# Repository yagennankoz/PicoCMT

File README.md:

**日本語** | [English](README_en.md)

# PicoCmt - 8bit PC用 CMT(カセット磁気テープ) エミュレータ

Raspberry Pi Pico W を使用した、8bitレトロPC向けのカセット磁気テープ（CMT）エミュレータです。
SDカードに保存されたテープイメージファイルを実機へ音声信号としてロードしたり、実機からのセーブ音声を録音してテープイメージに変換・保存することができます。
Wi-Fi経由で、PCやスマホのブラウザからSDカードのファイルを操作したり、USBでつないだPCからSDカードをUSBドライブとして読み書きしたりすることもできます。

## 主な機能
* **ファイルからの再生 (LOAD)**
  * 対応フォーマット:

    | 拡張子         | 主な機種                                                      | 実機での確認       |
    | -------------- | ------------------------------------------------------------- | ------------------ |
    | `.T88`         | PC-8801 / PC-8001 (タグ形式)                                  | 確認済み (PC-8801) |
    | `.CMT`         | PC-8801 / PC-8001 (ベタ形式)                                  | 確認済み (PC-8801) |
    | `.P6` / `.P6T` | PC-6001                                                       | **未確認**         |
    | `.CAS`         | MSX                                                           | 確認済み           |
    | `.T77`         | FM-7                                                          | **未確認**         |
    | `.RAW`         | 機種を問わない (録音したままの波形。PicoCmt 独自の形式)       | 確認済み (PC-8801) |
    | `.WAV`         | 機種を問わない (テープの音声を録った WAV ファイル。リニアPCM) | 確認済み (PC-8801) |

    PC-6001 (`.P6` / `.P6T`) と FM-7 (`.T77`) は、実機でもエミュレータでも動作確認をしていません。
    MP3 などの圧縮した音声には対応していません。
    WAV は波形をそのまま出すので、録音の状態が悪いと読めないことがあります。そのときは T88 などに変換してから再生してください (変換するときれいな波形で出し直します)。
  * ファイル内のデータをFSK音声信号に変換し、PCへ出力します。
  * PCのREMOTE端子 (カセットのモーター制御) に連動して、再生の開始・一時停止を自動で行います。
  * T88 は無音区間 (ブランク) の前後へ頭出しできます。
  * T88 の DATA タグの形式 (ボーレート・パリティ・ストップビット長) どおりに出力します。
  * 一覧に出すファイルを拡張子で絞り込めます。
* **実機からの録音・変換 (SAVE)**
  * PCからの出力音声を録音し、自動的に上記のいずれかの形式に変換してSDカードに保存します。
  * ボーレート (600 / 1200 / 2400) は録音した信号から自動で判別します。
  * 録音したデータに含まれるプログラム名を読み取り、ファイル名を自動で付けます。
  * 既存ファイルへの追記録音 (アペンド) にも対応しています (`.T88` / `.T77` / `.CAS` / `.P6T`)。
  * 1つのブロックの中で 600 / 1200 ボーが切り替わるテープや、パリティ付きのデータも `.T88` に記録できます。
  * 変換せずに、録音したままの波形を `.RAW` として保存することもできます。形式は [RAW_FORMAT.md](RAW_FORMAT.md) を参照してください。
* **RAW / WAV からの変換**
  * `.RAW` と `.WAV` を、本体で上の各形式に変換できます。データの中のプログラム名でファイル名を付けます。
* **Wi-Fi / Webファイルマネージャ機能**
  * Pico W のWi-Fi機能を利用し、内蔵のWebサーバーを起動できます。
  * SDカードを抜き差しすることなく、PCやスマホのブラウザから `http://picocmt.local/` を開いて、ファイルのアップロード・ダウンロード・削除・名前の変更・フォルダの作成ができます。
  * 複数のファイルをまとめて選ぶと、1つずつ順番にアップロード・ダウンロードします。
  * ログイン (ID/パスワード) の ON/OFF とパスワードは本体の設定メニューで変更できます。
  * Wi-Fi接続中はNTPで時刻を合わせ、録音したファイルに日時を付けます (日本版は日本時間、全世界共通版はUTC)。
  * 再生・録音中は、Wi-Fiの通信で電源が揺れて信号が乱れないよう、Wi-Fiを自動で切断し、終わったらつなぎ直します。
  * **Wi-Fiを使うときは、ACアダプタ (USB充電器) など、電流に余裕のある電源の使用をお勧めします。** Wi-Fiの通信には大きな電流が流れるため、PCのUSB端子やUSBハブからの給電では動作が不安定になることがあります。
  * 設定したWi-Fiパスワード等は、本体固有のIDで暗号化してEEPROMに保存します。
    ただし、本体を入手した人はフラッシュメモリから取り出せる可能性があります。気になる場合は、ゲスト用やIoT機器用のWi-Fiを使ってください。
* **USBドライブ機能**
  * USBでPCにつなぐと、SDカードをPCのUSBドライブとして読み書きできます (SDカードを抜き差しせずにファイルをコピー・削除できます)。
  * 電源を入れたときにPCとつながっていれば、USBドライブにするかを最初に聞きます。設定メニューからも始められます。
  * USBドライブの間は、SDカードが壊れないよう、再生・録音・ファイルブラウザを止め、Wi-Fiも切断します。PCで取り出すか、本体の [STOP] でやめると元に戻ります。

---

## 必要なハードウェア

基板のガーバーデータは`hardware/JLCPCB`を参照してください。JLCPCB等に発注することでプリント基板の生産が可能です。
主要な部品構成は以下の通りです。詳細な部品リストや定数は `hardware/parts.md` を参照してください。

* **マイコンボード:** Raspberry Pi Pico W
  * **電源:** PCのUSB端子やUSBハブ (セルフパワーのものも含む) から給電していると、Wi-Fiの通信で電源が不安定になり、ロード・セーブがエラーになることがあるため (PC-8801 で確認)、ロード・セーブ中はWi-Fiを自動で切断します。**Wi-Fiを使うときは、ACアダプタ (USB充電器) など、電流に余裕のある電源から給電してください。**
* **ディスプレイ:** 0.96インチ OLEDディスプレイ (SSD1306 / I2C接続)
* **ストレージ:** MicroSDカードモジュール (SPI接続)
* **アナログ回路:** 
  * オペアンプ `MCP6022` (信号増幅・波形整形用)
  * コンパレータ `LM393` (録音パルス検出用)
  * フォトカプラ `PC817` (REMOTE端子制御用)
* **インターフェース:**
  * タクトスイッチ ×10 (操作用)
  * 3.5mm モノラルジャック ×2 (LOAD用, SAVE用)
  * 2.5mm モノラルジャック ×1 (REMOTE制御用)
  * 圧電ブザー (モニタースピーカー用)

---

## 開発環境とビルド手順

本プロジェクトは **PlatformIO** を使用して開発されています。Arduinoコアには `earlephilhower` 版の Raspberry Pi PicoW/RP2040 コアを使用します。

### 1. インストール
1. リリースに配置されているファームウェアファイル`PicoCMT*.uf2`をダウンロードします。
   ファイル名の末尾は地域の設定です。使う国に合わせて選んでください。

   | ファイル         | 使う国       | Wi-Fiの地域設定        | 時刻                          |
   | ---------------- | ------------ | ---------------------- | ----------------------------- |
   | `PicoCMT_JP.uf2` | 日本         | 日本 (チャンネル1〜13) | 日本時間 (NTP: `ntp.nict.jp`) |
   | `PicoCMT_WW.uf2` | 日本以外の国 | 全世界共通             | UTC (NTP: `pool.ntp.org`)     |
2. PCとRaspberryPi PicoWをUSB接続します。
3. RaspberryPi PicoWの`BOOTSEL`ボタンを押しながら、PicoCMT基板上のRESETボタンを押下します。
4. PC上でRaspberryPi PicoWのフォルダが開かれますので、そこに`PicoCMT*.uf2`をコピーします。
5. RaspberryPi PicoWが自動で再起動され、PicoCMTが起動します。

以前のバージョン (Wi-Fi設定にPINコードを使っていたもの) から更新した場合、保存していたWi-Fi設定は使えなくなります。もう一度設定してください。

### 2. 開発環境の準備
以下はソースコードからビルドする際の手順です。通常は不要です。
1. [Visual Studio Code (VSCode)](https://code.visualstudio.com/) をインストールします。
2. VSCodeの拡張機能から **PlatformIO IDE** をインストールします。
3. リポジトリをクローンしてください。

### 3. PIOファイルのコンパイルについて
PicoのPIO（アセンブリ）コードは、ビルド前に自動的にC/C++のヘッダファイルに変換される仕組みになっています。
`platformio.ini` 内の `extra_scripts = pre:scripts/generate_pio_headers.py` により、ビルド時に自動で `pio/` フォルダ内のファイルが処理され、`include/generated/` ディレクトリにヘッダファイルが出力されます。手動で実行する必要はありません。

### 4. ビルド
1. VSCodeで `PicoCmt` フォルダを開きます。
2. 初回起動時、PlatformIOが自動的に必要なツールチェーンとライブラリ（Adafruit GFX, SSD1306等）をダウンロードします。
3. 画面下のPlatformIOツールバーから **[✓] Build** をクリックしてビルドを実行します。
   地域ごとの2つのファームウェアがまとめてビルドされ、`.pio/build/<環境名>/PicoCMT_<地域>.uf2` に出力されます。

| 環境名       | 出力ファイル     | Wi-Fiの地域設定                        | 時刻                      |
| ------------ | ---------------- | -------------------------------------- | ------------------------- |
| `rpipico_ww` | `PicoCMT_WW.uf2` | 全世界共通 (`CYW43_COUNTRY_WORLDWIDE`) | UTC                       |
| `rpipico_jp` | `PicoCMT_JP.uf2` | 日本 (`CYW43_COUNTRY_JAPAN`)           | 日本時間 (`FW_REGION_JP`) |

書き込み (Upload) は環境を1つ指定して行ってください。例: `pio run -e rpipico_jp -t upload`

---

## 使い方・操作方法

操作方法については、付属の **[操作マニュアル](MANUAL.md)** を参照してください。
基本的なUI操作、再生（LOAD）・録音（SAVE）の手順、ボーレートの変更方法、Wi-Fi/Webファイルマネージャの設定方法、USBドライブの使い方について記載されています。

---

## 注意事項・免責事項

* 本デバイスの接続や使用により発生したいかなる損害（レトロPC本体の故障、データの消失など）についても、開発者は責任を負いません。自己責任でご使用ください。
* PC-6001 (`.P6` / `.P6T`) と FM-7 (`.T77`) は、実機・エミュレータでの動作確認をしていません。
* **Wi-Fiを使うときは、ACアダプタ (USB充電器) など、電流に余裕のある電源から給電してください。** PCのUSB端子やUSBハブからの給電では、Wi-Fiの通信で電源が不安定になることがあります。
* ロード・セーブ中はWi-Fiを自動で切断します (Wi-Fiの通信で電源が不安定になり、レトロPCへのロード・セーブがエラーになることがあるため。PC-8801 で確認)。
* Webファイルマネージャは暗号化されていない通信 (HTTP) を使います。家庭内のネットワークでお使いください。
* 本体を人に譲る・手放すときは、設定メニューの `WiFi Config` (アクセスポイントを選ぶ画面で [LEFT]) で、保存されているWi-Fi設定を消去してください。
* USBドライブの間に、PCで取り出さずにUSBケーブルを抜いたりSDカードを抜いたりすると、書き込み中のファイルが壊れることがあります。

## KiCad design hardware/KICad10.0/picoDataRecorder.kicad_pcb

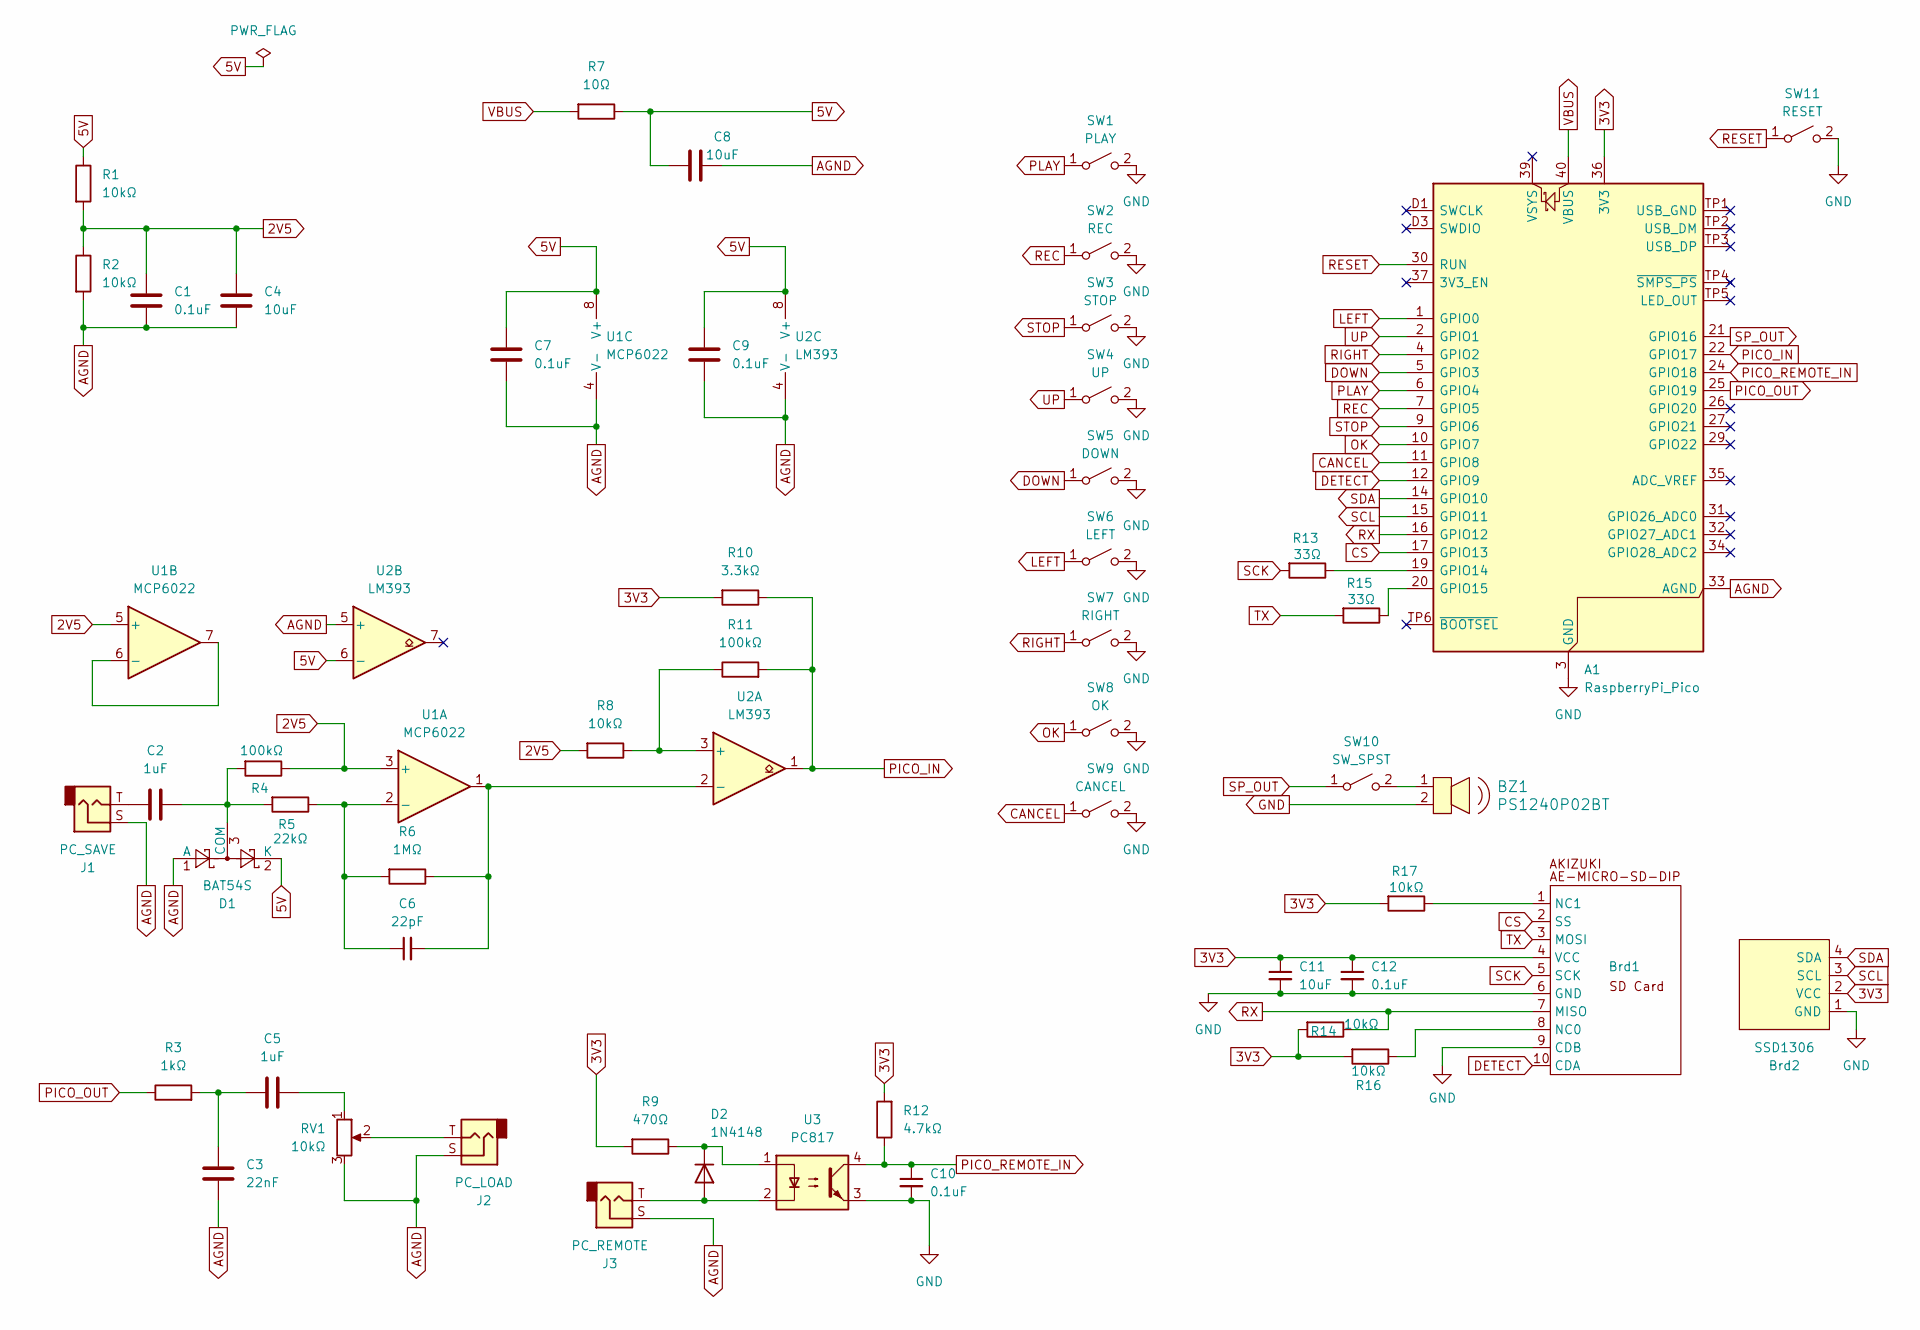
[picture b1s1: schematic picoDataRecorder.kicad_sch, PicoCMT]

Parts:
A1: RaspberryPi_Pico; RaspberryPi_Pico_Common_Unspecified
BZ1: PS1240P02BT; Piezo_Transducer_THT_PS1240P02BT; MPN PS1240P02BT; Digi-Key_PN 445-2525-1-ND
Brd1: AE-MICRO-SD-DIP
Brd2: SSD1306; 128x64OLED
C1, C7, C9, C10, C12: 0.1uF; C_0603_1608Metric_Pad1.08x0.95mm_HandSolder; LCSC C14663
C2, C5: 1uF; C_0603_1608Metric_Pad1.08x0.95mm_HandSolder; LCSC C15849
C3: 22nF; C_0603_1608Metric_Pad1.08x0.95mm_HandSolder; LCSC C21122
C4, C8, C11: 10uF; C_0603_1608Metric_Pad1.08x0.95mm_HandSolder; LCSC C19702
C6: 22pF; C_0603_1608Metric_Pad1.08x0.95mm_HandSolder; LCSC C1653
D1: BAT54S; SOT-23; LCSC C83935
D2: 1N4148; Nexperia_CFP3_SOD-123W; LCSC C81598
J1: PC_SAVE; 3.5mm Jack MONO TS
J2: PC_LOAD; 3.5mm Jack MONO TS
J3: PC_REMOTE; 2.5mm Jack MONO TS
R1, R2, R8, R14, R16, R17: 10kΩ; R_0603_1608Metric_Pad0.98x0.95mm_HandSolder; LCSC C25804
R3: 1kΩ; R_0603_1608Metric_Pad0.98x0.95mm_HandSolder; LCSC C21190
R4, R11: 100kΩ; R_0603_1608Metric_Pad0.98x0.95mm_HandSolder; LCSC C25803
R5: 22kΩ; R_0603_1608Metric_Pad0.98x0.95mm_HandSolder; LCSC C31850
R6: 1MΩ; R_0603_1608Metric_Pad0.98x0.95mm_HandSolder; LCSC C22935
R7: 10Ω; R_0603_1608Metric_Pad0.98x0.95mm_HandSolder; LCSC C22859
R9: 470Ω; R_0603_1608Metric_Pad0.98x0.95mm_HandSolder; LCSC C23179
R10: 3.3kΩ; R_0603_1608Metric_Pad0.98x0.95mm_HandSolder; LCSC C22978
R12: 4.7kΩ; R_0603_1608Metric_Pad0.98x0.95mm_HandSolder; LCSC C23162
R13, R15: 33Ω; R_0603_1608Metric_Pad0.98x0.95mm_HandSolder; LCSC C23140
RV1: 10kΩ; Potentiometer_Runtron_RM-065_Vertical
SW1: PLAY; SW_PUSH_6mm_H4.3mm
SW2: REC; SW_PUSH_6mm_H4.3mm
SW3: STOP; SW_PUSH_6mm_H4.3mm
SW4: UP; SW_PUSH_6mm_H4.3mm
SW5: DOWN; SW_PUSH_6mm_H4.3mm
SW6: LEFT; SW_PUSH_6mm_H4.3mm
SW7: RIGHT; SW_PUSH_6mm_H4.3mm
SW8: OK; SW_PUSH_6mm_H4.3mm
SW9: CANCEL; SW_PUSH_6mm_H4.3mm
SW10: SW_SPST; SW_DIP_SPSTx01_Slide_9.78x4.72mm_W7.62mm_P2.54mm
SW11: RESET; SW_PUSH_6mm_H4.3mm
U1: MCP6022; DIP-8_W7.62mm_Socket
U2: LM393; DIP-8_W7.62mm_Socket
U3: PC817; DIP-4_W7.62mm_Socket

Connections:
2V5: C1.1, C4.1, R1.2, R2.1, R4.1, R8.2, U1.3 (+), U1.5 (+)
3V3: A1.36 (3V3), Brd1.4 (VCC), Brd2.2 (VCC), C11.1, C12.1, R9.2, R10.2, R12.2, R14.2, R16.2, R17.2
5V: C7.1, C8.2, C9.1, D1.2 (K), R1.1, R7.1, U1.8 (V+), U2.6 (-), U2.8 (V+)
AGND: A1.33 (AGND), C1.2, C3.2, C4.2, C7.2, C8.1, C9.2, D1.1 (A), J1.S, J2.S, J3.S, R2.2, RV1.3, U1.4 (V-), U2.4 (V-), U2.5 (+)
CANCEL: A1.11 (GPIO8), SW9.1 (A)
CS: A1.17 (GPIO13), Brd1.2 (SS)
DETECT: A1.12 (GPIO9), Brd1.10 (CDA)
DOWN: A1.5 (GPIO3), SW5.1 (A)
GND: A1.3 (GND), A1.8 (GND), A1.13 (GND), A1.18 (GND), A1.23 (GND), A1.28 (GND), A1.38 (GND), A1.D2 (GND), BZ1.2, Brd1.6 (GND), Brd1.9 (CDB), Brd2.1 (GND), C10.2, C11.2, C12.2, SW1.2 (B), SW2.2 (B), SW3.2 (B), SW4.2 (B), SW5.2 (B), SW6.2 (B), SW7.2 (B), SW8.2 (B), SW9.2 (B), SW11.2 (B), U3.3
LEFT: A1.1 (GPIO0), SW6.1 (A)
unnamed: A1.19 (GPIO14), R13.1
unnamed: A1.20 (GPIO15), R15.1
unnamed: Brd1.8 (NC0), R16.1
unnamed: Brd1.1 (NC1), R17.1
unnamed: C2.2, J1.T
unnamed: C3.1, C5.1, R3.2
unnamed: C5.2, RV1.1
unnamed: C2.1, D1.3 (COM), R4.2, R5.2
unnamed: D2.2 (A), J3.T, U3.2
unnamed: D2.1 (K), R9.1, U3.1
unnamed: J2.T, RV1.2
unnamed: BZ1.1, SW10.2 (B)
unnamed: C6.1, R5.1, R6.2, U1.2 (-)
unnamed: U1.6 (-), U1.7
unnamed: R8.1, R11.1, U2.3 (+)
unnamed: C6.2, R6.1, U1.1, U2.2 (-)
OK: A1.10 (GPIO7), SW8.1 (A)
PICO_IN: A1.22 (GPIO17), R10.1, R11.2, U2.1
PICO_OUT: A1.25 (GPIO19), R3.1
PICO_REMOTE_IN: A1.24 (GPIO18), C10.1, R12.1, U3.4
PLAY: A1.6 (GPIO4), SW1.1 (A)
REC: A1.7 (GPIO5), SW2.1 (A)
RESET: A1.30 (RUN), SW11.1 (A)
RIGHT: A1.4 (GPIO2), SW7.1 (A)
RX: A1.16 (GPIO12), Brd1.7 (MISO), R14.1
SCK: Brd1.5 (SCK), R13.2
SCL: A1.15 (GPIO11), Brd2.3 (SCL)
SDA: A1.14 (GPIO10), Brd2.4 (SDA)
SP_OUT: A1.21 (GPIO16), SW10.1 (A)
STOP: A1.9 (GPIO6), SW3.1 (A)
TX: Brd1.3 (MOSI), R15.2
UP: A1.2 (GPIO1), SW4.1 (A)
VBUS: A1.40 (VBUS), R7.2

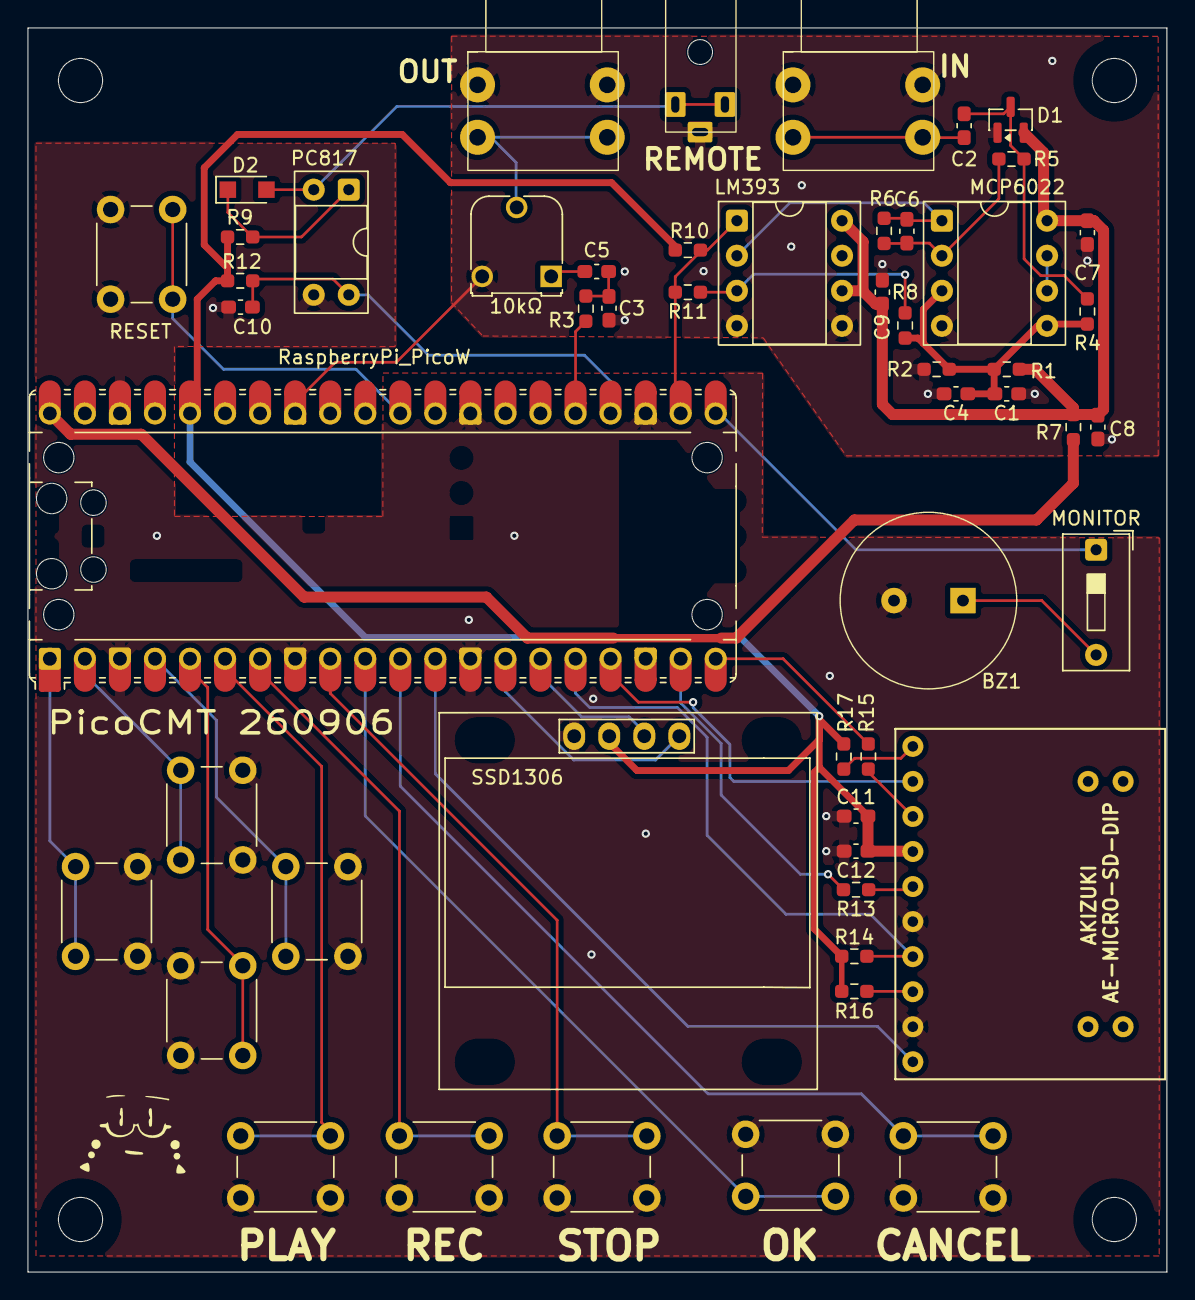
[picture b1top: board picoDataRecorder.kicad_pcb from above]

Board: 2 copper layers, 82.6 x 90.2 mm, 53 parts (0 on the bottom side), 43 nets.

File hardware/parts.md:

## カテゴリ別 部品リスト
実装や部品手配の際にご活用いただけるよう、種類別に分類しました。
抵抗とコンデンサのフットプリントは、表面実装の**1608サイズ (1.6mm×0.8mm)**の手はんだ（HandSolder）用パッド指定になっています。

### マイコン・モジュール類
* **RaspberryPi Pico W** ×1 (A1)
* **AE-MICRO-SD-DIP** (秋月電子MicroSDモジュール) ×1 (Brd1)
* **SSD1306** (128x64 OLEDディスプレイ) ×1 (Brd2)

### IC・半導体
* **MCP6022** (オペアンプ DIP-8) ×1 (U1)
* **LM393** (コンパレータ DIP-8) ×1 (U2)
* **PC817** (フォトカプラ DIP-4) ×1 (U3)
* **BAT54S** (ショットキーダイオード SOT-23) ×1 (D1)
* **1N4148** (スイッチングダイオード SOD-123W) ×1 (D2)

### 抵抗器 (0603 (1608M) SMD)
* **10Ω** ×1 (R7)
* **33Ω** ×2 (R13, R15)
* **470Ω** ×1 (R9)
* **1kΩ** ×1 (R3)
* **3.3kΩ** ×1 (R10)
* **4.7kΩ** ×1 (R12)
* **10kΩ** ×6 (R1, R2, R8, R14, R16, R17)
* **22kΩ** ×1 (R5)
* **100kΩ** ×2 (R4, R11)
* **1MΩ** ×1 (R6)

### 半固定抵抗 (ポテンショメータ)
* **10kΩ** 縦型(RM-065) ×1 (RV1)

### コンデンサ (0603 (1608M) SMD)
* **22pF** ×1 (C6)
* **22nF** ×1 (C3)
* **0.1uF** ×5 (C1, C7, C9, C10, C12)
* **1uF** ×2 (C2, C5)
* **10uF** ×3 (C4, C8, C11)

### スイッチ類
* **タクトスイッチ 6mm (H=4.3mm)** ×10 
  *(SW1〜SW9, SW11 / PLAY, REC, STOP, UP, DOWN, LEFT, RIGHT, OK, CANCEL, RESET)*
* **スライドスイッチ (SPST ディップスイッチ)** ×1 (SW10)

### コネクタ・その他
* **3.5mm モノラルジャック** RS PRO 3.5mmジャック/PCBマウント(913-1011) ×2 (J1 / SAVE, J2 / LOAD)
* **2.5mm モノラルジャック** RS PRO 2.5mmジャック/PCBマウント(913-1005) ×1 (J3 / REMOTE)
* **PS1240P02BT** (圧電ブザー スルーホール PS1240P02BT) ×1 (BZ1)

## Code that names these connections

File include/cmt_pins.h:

#pragma once

// GPIO pin assignments
#define PICO_IN_PIN      17  // CMT input
#define PICO_OUT_PIN     19  // CMT output
#define REMOTE_PIN       18  // Remote detect input
#define BUZZER_PIN       16

#define PICO_I2C_SDA_PIN 10 // OLED I2C SDA
#define PICO_I2C_SCL_PIN 11 // OLED I2C SCL

#define PICO_SD_CS_PIN   13  // SD card SPI CS
#define PICO_SPI_MISO_PIN 12 // SD card SPI MISO(RX)
#define PICO_SPI_MOSI_PIN 15 // SD card SPI MOSI(TX)
#define PICO_SPI_CLK_PIN  14 // SD card SPI SCK
#define PICO_SPI_DETECT_PIN 9 // SD card detect input

#define BTN_REC_PIN      5
#define BTN_PLAY_PIN     4
#define BTN_STOP_PIN     6
#define BTN_OK_PIN       7
#define BTN_CANCEL_PIN   8
#define BTN_UP_PIN       1
#define BTN_DOWN_PIN     3
#define BTN_LEFT_PIN     0
#define BTN_RIGHT_PIN    2
#define NUM_BUTTONS      9
